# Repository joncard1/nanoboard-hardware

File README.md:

# nanoboard-hardware
This project tracks the development of the hardware for the nanoboard project. It uses Eagle to view the schematic and board layouts. It is tracked in a separate submodule to be consistent with the other submodules, which needed to be separated to aid in compilation.

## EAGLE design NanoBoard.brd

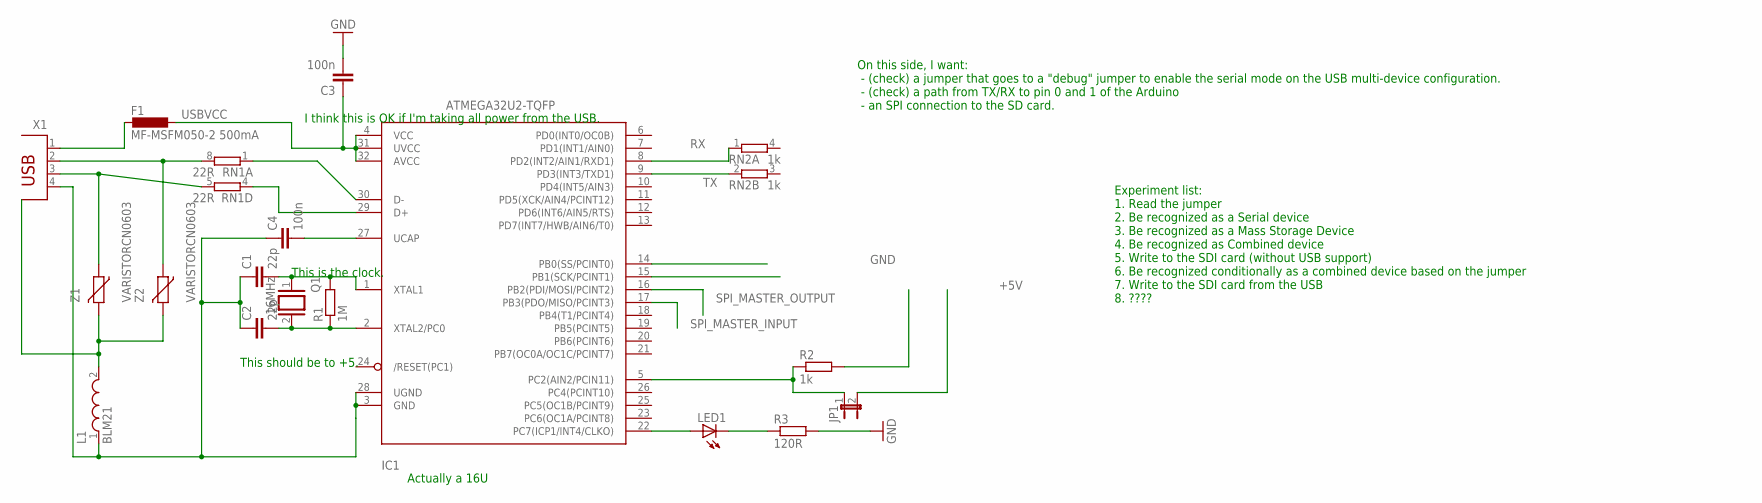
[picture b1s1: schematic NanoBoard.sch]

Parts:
C1, C2: 22p; C2.5-2
C3: 100n; C2.5-2
C4: 100n; C2.5-3
F1: MF-MSFM050-2 500mA; L1812
IC1: ATMEGA32U2-TQFP; TQFP32-08
JP1: JP1E; JP1
L1: BLM21; WE-CBF_0805(W=3.0)
LED1: LED; SMARTLED-TTW
Q1: 16MHz; QS
R1: 1M; R0603
R2: 1k; 0204V
R3: 120R; 0204V
RN1: 22R; CAY16
RN2: 1k; EXB14V
X1: PN61729
Z1, Z2: VARISTORCN0603; CT/CN0603

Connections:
+5V: JP1.2
GND: C3.2, R2.2, R3.2
unnamed: F1.2, X1.1
unnamed: RN1.8 (2), X1.2, Z2.1
unnamed: RN1.5 (2), X1.3, Z1.1
unnamed: L1.2, Z1.2, Z2.2
unnamed: C4.2, IC1.27 (UCAP)
unnamed: IC1.30 (D-), RN1.1
unnamed: IC1.29 (D+), RN1.4 (1)
unnamed: C1.2, IC1.1 (XTAL1), Q1.1, R1.2
unnamed: C2.2, IC1.2 (XTAL2/PC0), Q1.2, R1.1
unnamed: C1.1, C2.1, C4.1, IC1.3 (GND), IC1.28 (UGND), L1.1, X1.4
unnamed: IC1.5 (PC2(AIN2/PCIN11)), JP1.1, R2.1
unnamed: IC1.22 (PC7(ICP1/INT4/CLKO)), LED1.A@1 (A)
unnamed: LED1.C@1 (C), R3.1
RX: IC1.8 (PD2(INT2/AIN1/RXD1)), RN2.1
SPI_MASTER_INPUT: IC1.17 (PB3(PDO/MISO/PCINT3))
SPI_MASTER_OUTPUT: IC1.16 (PB2(PDI/MOSI/PCINT2))
TX: IC1.9 (PD3(INT3/TXD1)), RN2.2 (1)
USBVCC: C3.1, F1.1, IC1.4 (VCC), IC1.31 (UVCC), IC1.32 (AVCC)

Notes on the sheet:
Actually a 16U
This should be to +5.
This is the clock.
I think this is OK if I'm taking all power from the USB.
On this side, I want: - (check) a jumper that goes to a "debug" jumper to enable the serial mode on the USB multi-device configuration. - (check) a path from TX/RX to pin 0 and 1 of the Arduino - an SPI connection to the SD card.
Experiment list: 1. Read the jumper 2. Be recognized as a Serial device 3. Be recognized as a Mass Storage Device 4. Be recognized as Combined device 5. Write to the SDI card (without USB support) 6. Be recognized conditionally as a combined device based on the jumper 7. Write to the SDI card from 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

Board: 2 copper layers, 18 parts (0 on the bottom side), 17 nets, no tracks yet.

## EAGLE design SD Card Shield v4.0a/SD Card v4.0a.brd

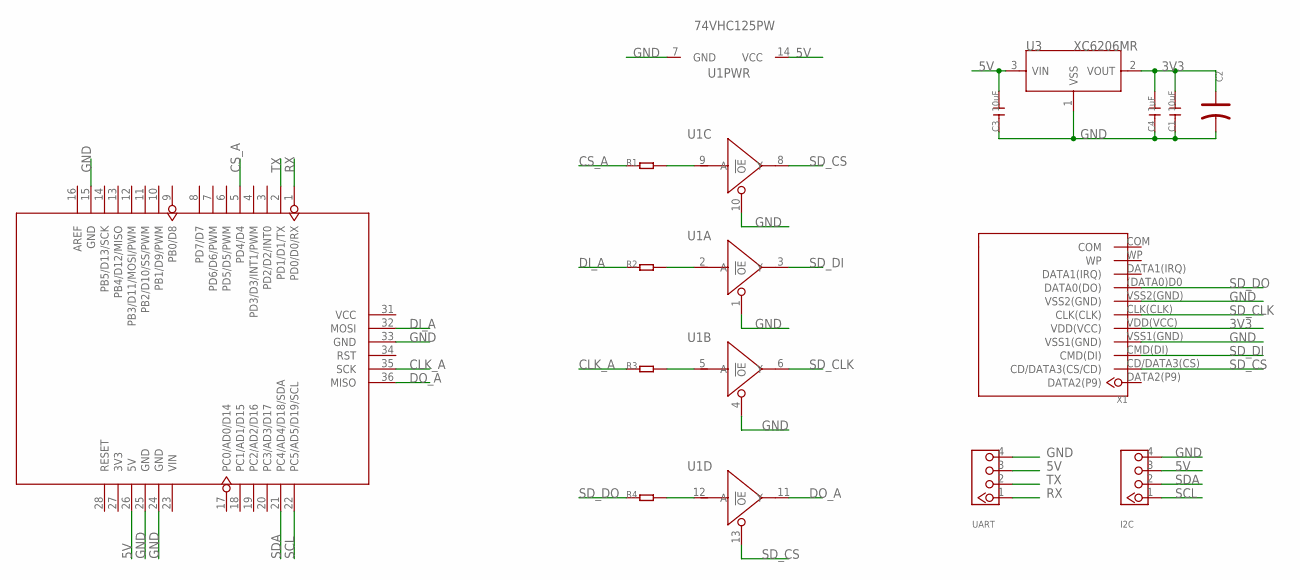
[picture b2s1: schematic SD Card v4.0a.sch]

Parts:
C1, C3: 10uF; C0805
C2: CAP-AVX-A; AVX-A
C4: 1uF; C0805
I2C: TWIG-4P-2.0-2.0; 4P-2.0
R1, R2, R3, R4: R-0603; R0603
U1: 74VHC125PW; TSSOP14
U2: ARDUINO'W/-SILK; ARDUINO
U3: XC6206MR; SOT23
UART: TWIG-4P-2.0-2.0; 4P-2.0
X1: SDCARDEXTDEVICE; SDCARDEXTPACKAGE

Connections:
3V3: C1.2, C2.+, C4.2, U3.2 (VOUT), X1.VDD(VCC)
5V: C3.2, I2C.3, U1.14 (VCC), U2.26 (5V), U3.3 (VIN), UART.3
CLK_A: R3.1, U2.35 (SCK)
CS_A: R1.1, U2.5 (PD4/D4)
DI_A: R2.1, U2.32 (MOSI)
DO_A: U1.11 (Y), U2.36 (MISO)
GND: C1.1, C2.-, C3.1, C4.1, I2C.4, U1.1 (!OE), U1.4 (!OE), U1.7 (GND), U1.10 (!OE), U2.15 (GND), U2.24 (GND), U2.25 (GND), U2.33 (GND), U3.1 (VSS), UART.4, X1.VSS1(GND), X1.VSS2(GND)
unnamed: R4.2, U1.12 (A)
unnamed: R3.2, U1.5 (A)
unnamed: R2.2, U1.2 (A)
unnamed: R1.2, U1.9 (A)
RX: U2.1 (PD0/D0/RX), UART.1
SCL: I2C.1, U2.22 (PC5/AD5/D19/SCL)
SDA: I2C.2, U2.21 (PC4/AD4/D18/SDA)
SD_CLK: U1.6 (Y), X1.CLK(CLK)
SD_CS: U1.8 (Y), U1.13 (!OE), X1.CD/DATA3(CS) (CD/DATA3(CS/CD))
SD_DI: U1.3 (Y), X1.CMD(DI)
SD_DO: R4.1, X1.(DATA0)D0 (DATA0(DO))
TX: U2.2 (PD1/D1/TX), UART.2

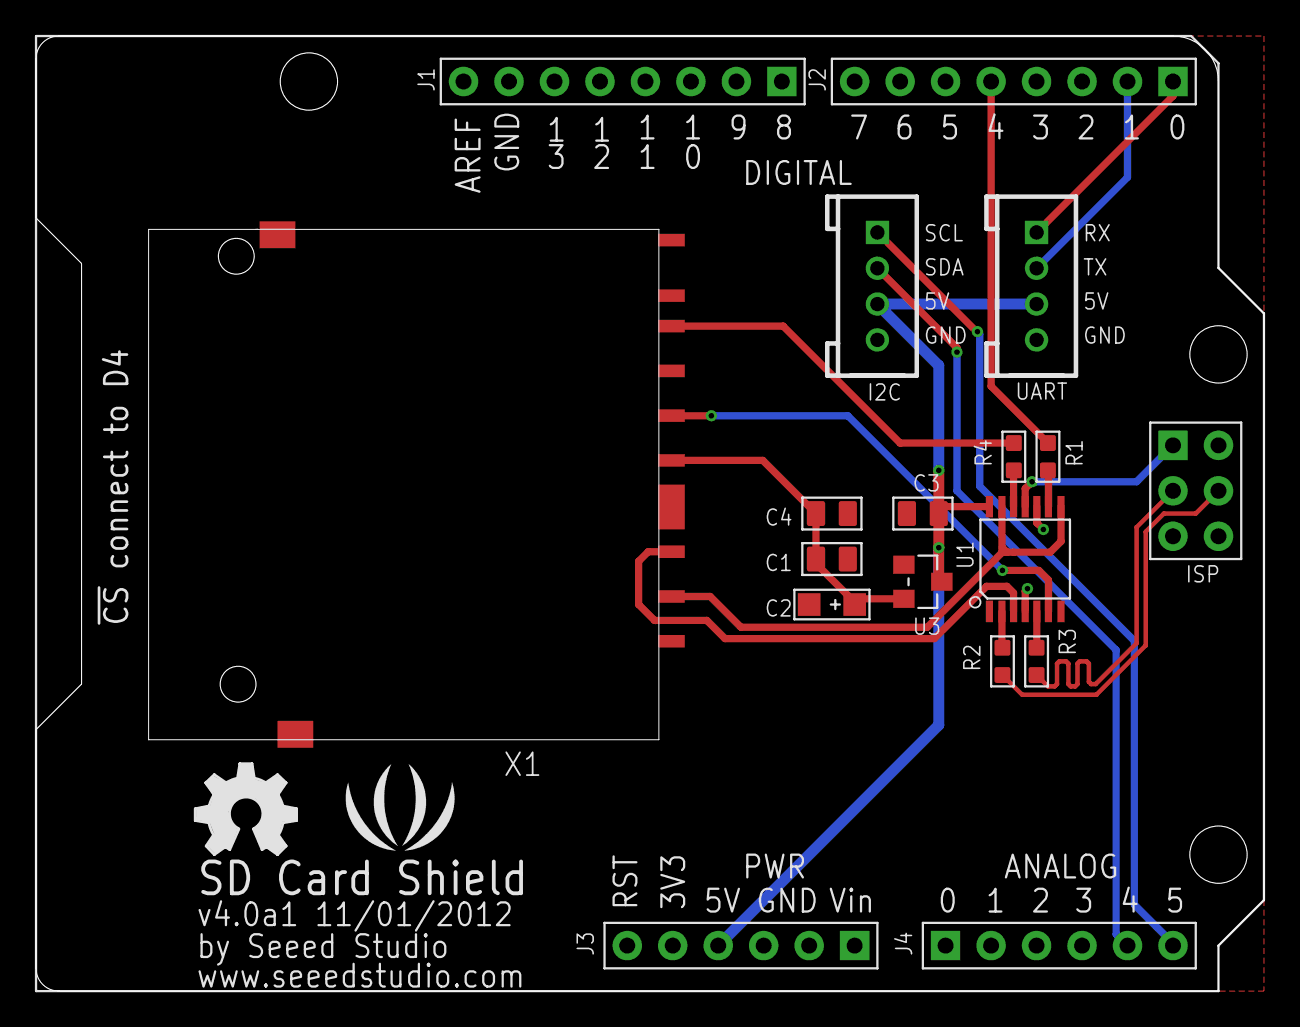
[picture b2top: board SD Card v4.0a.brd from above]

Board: 2 copper layers, 68.6 x 53.3 mm, 16 parts (0 on the bottom side), 19 nets.

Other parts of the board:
U$1: OSHW_FILLX200_NOTEXT
U$2: LOGO_SILK

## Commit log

2015-07-08 I forgot to include a README file.
2015-07-09 Initial commit of files.
    This includes a bunch of reference files as well as the important files, NanoBoard.x
2015-07-21 Fixed some errors Eagle discovered, and changed the pins the LED is on because they are analog pins.

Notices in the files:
parts and their libraries:
Wurth_Elektronik_Passive_rev15b: Copyright: Würth Elektronik
